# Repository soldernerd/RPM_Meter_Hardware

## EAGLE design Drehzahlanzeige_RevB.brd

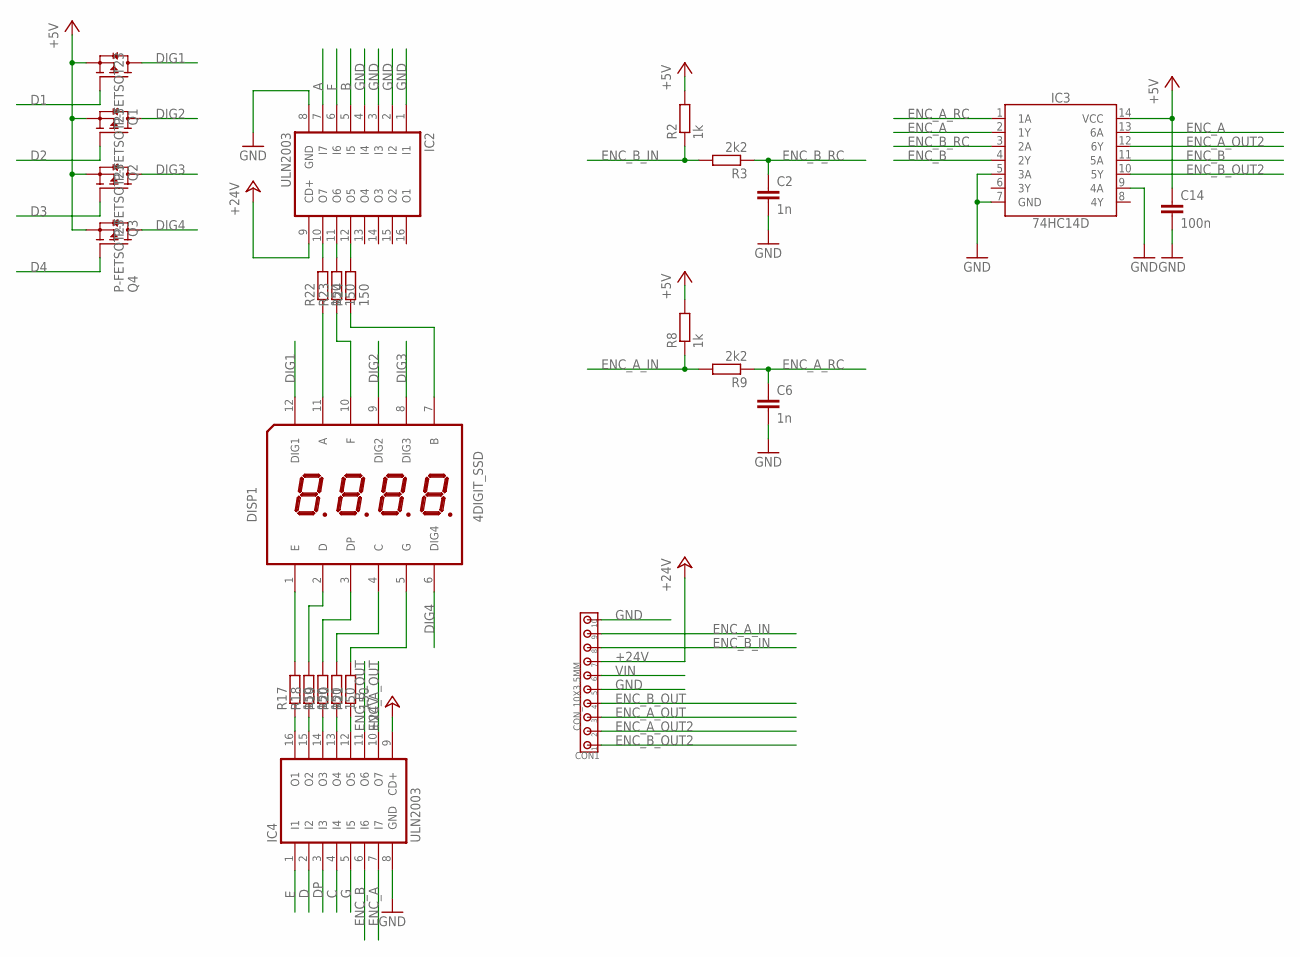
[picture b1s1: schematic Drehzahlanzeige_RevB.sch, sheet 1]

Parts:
C2, C6: 1n; C0805
C14: 100n; C0805
CON1: CON_10X3.5MM; 3.5MM_10X
DISP1: 4DIGIT_SSD
IC2, IC4: ULN2003; SO16
IC3: 74HC14D; SO14
Q1, Q2, Q3, Q4: P-FETSOT23; SOT23
R2, R8: 1k; R0805
R3, R9: 2k2; R0805
R17, R18, R19, R20, R21, R22, R23, R24: 150; R0805

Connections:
+5V: C14.1, IC3.14 (VCC), Q1.2 (S), Q2.2 (S), Q3.2 (S), Q4.2 (S), R2.2, R8.2; also elsewhere on the board
+24V: CON1.7, IC2.9 (CD+), IC4.9 (CD+); also elsewhere on the board
A: IC2.7 (I7); also elsewhere on the board
B: IC2.5 (I5); also elsewhere on the board
C: IC4.4 (I4); also elsewhere on the board
D: IC4.2 (I2); also elsewhere on the board
D1: Q1.1 (G); also elsewhere on the board
D2: Q2.1 (G); also elsewhere on the board
D3: Q3.1 (G); also elsewhere on the board
D4: Q4.1 (G); also elsewhere on the board
DIG1: DISP1.12 (DIG1), Q1.3 (D)
DIG2: DISP1.9 (DIG2), Q2.3 (D)
DIG3: DISP1.8 (DIG3), Q3.3 (D)
DIG4: DISP1.6 (DIG4), Q4.3 (D)
DP: IC4.3 (I3); also elsewhere on the board
E: IC4.1 (I1); also elsewhere on the board
ENC_A: IC3.2 (1Y), IC3.13 (6A), IC4.7 (I7); also elsewhere on the board
ENC_A_IN: CON1.9, R8.1, R9.2
ENC_A_OUT: CON1.3, IC4.10 (O7)
ENC_A_OUT2: CON1.2, IC3.12 (6Y)
ENC_A_RC: C6.1, IC3.1 (1A), R9.1
ENC_B: IC3.4 (2Y), IC3.11 (5A), IC4.6 (I6); also elsewhere on the board
ENC_B_IN: CON1.8, R2.1, R3.2
ENC_B_OUT: CON1.4, IC4.11 (O6)
ENC_B_OUT2: CON1.1, IC3.10 (5Y)
ENC_B_RC: C2.1, IC3.3 (2A), R3.1
F: IC2.6 (I6); also elsewhere on the board
G: IC4.5 (I5); also elsewhere on the board
GND: C2.2, C6.2, C14.2, CON1.5, CON1.10, IC2.1 (I1), IC2.2 (I2), IC2.3 (I3), IC2.4 (I4), IC2.8 (GND), IC3.5 (3A), IC3.7 (GND), IC3.9 (4A), IC4.8 (GND); also elsewhere on the board
unnamed: DISP1.1 (E), R17.2
unnamed: DISP1.2 (D), R18.2
unnamed: DISP1.3 (DP), R19.2
unnamed: DISP1.4 (C), R20.2
unnamed: DISP1.5 (G), R21.2
unnamed: DISP1.11 (A), R22.1
unnamed: DISP1.10 (F), R23.1
unnamed: DISP1.7 (B), R24.1
unnamed: IC4.16 (O1), R17.1
unnamed: IC4.15 (O2), R18.1
unnamed: IC4.14 (O3), R19.1
unnamed: IC4.13 (O4), R20.1
unnamed: IC4.12 (O5), R21.1
unnamed: IC2.10 (O7), R22.2
unnamed: IC2.11 (O6), R23.2
unnamed: IC2.12 (O5), R24.2
VIN: CON1.6; also elsewhere on the board

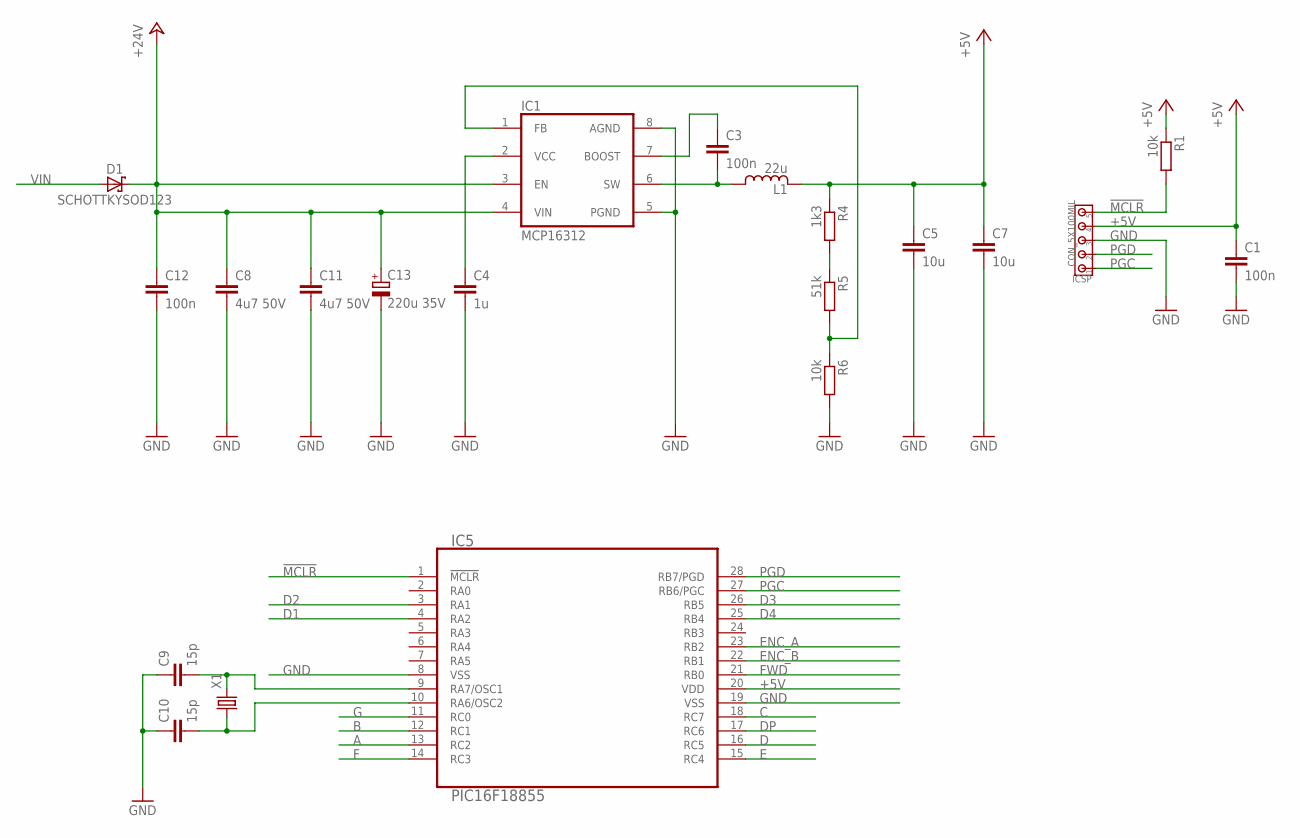
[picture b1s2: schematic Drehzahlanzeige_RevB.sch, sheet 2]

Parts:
C1, C3, C12: 100n; C0805
C4: 1u; C0805
C5, C7: 10u; C0805
C8, C11: 4u7 50V; C1206
C9, C10: 15p; C0805
C13: 220u 35V; 8MM
D1: SCHOTTKYSOD123; SOD123
IC1: MCP16312; MSOP8
IC5: PIC16F18855; SO28W
ICSP: CON_5X100MIL; 100MIL_5X
L1: 22u; LPS4018
R1, R6: 10k; R0805
R4: 1k3; R0805
R5: 51k; R0805
X1: CRYSTAL5X3.2MM; 5X3.2MM

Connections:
!MCLR!: IC5.1 (!MCLR!), ICSP.5, R1.2
+5V: C1.1, C5.1, C7.1, IC5.20 (VDD), ICSP.4, L1.2, R1.1, R4.1; also elsewhere on the board
+24V: C8.1, C11.1, C12.1, C13.+, D1.C, IC1.3 (EN), IC1.4 (VIN); also elsewhere on the board
A: IC5.13 (RC2); also elsewhere on the board
B: IC5.12 (RC1); also elsewhere on the board
BOOST: C3.1, IC1.7 (BOOST)
C: IC5.18 (RC7); also elsewhere on the board
D: IC5.16 (RC5); also elsewhere on the board
D1: IC5.4 (RA2); also elsewhere on the board
D2: IC5.3 (RA1); also elsewhere on the board
D3: IC5.26 (RB5); also elsewhere on the board
D4: IC5.25 (RB4); also elsewhere on the board
DP: IC5.17 (RC6); also elsewhere on the board
E: IC5.15 (RC4); also elsewhere on the board
ENC_A: IC5.23 (RB2); also elsewhere on the board
ENC_B: IC5.22 (RB1); also elsewhere on the board
F: IC5.14 (RC3); also elsewhere on the board
FWD: IC5.21 (RB0)
G: IC5.11 (RC0); also elsewhere on the board
GND: C1.2, C4.2, C5.2, C7.2, C8.2, C9.1, C10.1, C11.2, C12.2, C13.-, IC1.5 (PGND), IC1.8 (AGND), IC5.8 (VSS), IC5.19 (VSS), ICSP.3, R6.2; also elsewhere on the board
unnamed: IC1.1 (FB), R5.2, R6.1
unnamed: R4.2, R5.1
unnamed: C4.1, IC1.2 (VCC)
unnamed: C10.2, IC5.10 (RA6/OSC2), X1.1
unnamed: C9.2, IC5.9 (RA7/OSC1), X1.2
PGC: IC5.27 (RB6/PGC), ICSP.1
PGD: IC5.28 (RB7/PGD), ICSP.2
RA4: IC5.6 (RA4)
SWITCH: C3.2, IC1.6 (SW), L1.1
VIN: D1.A; also elsewhere on the board

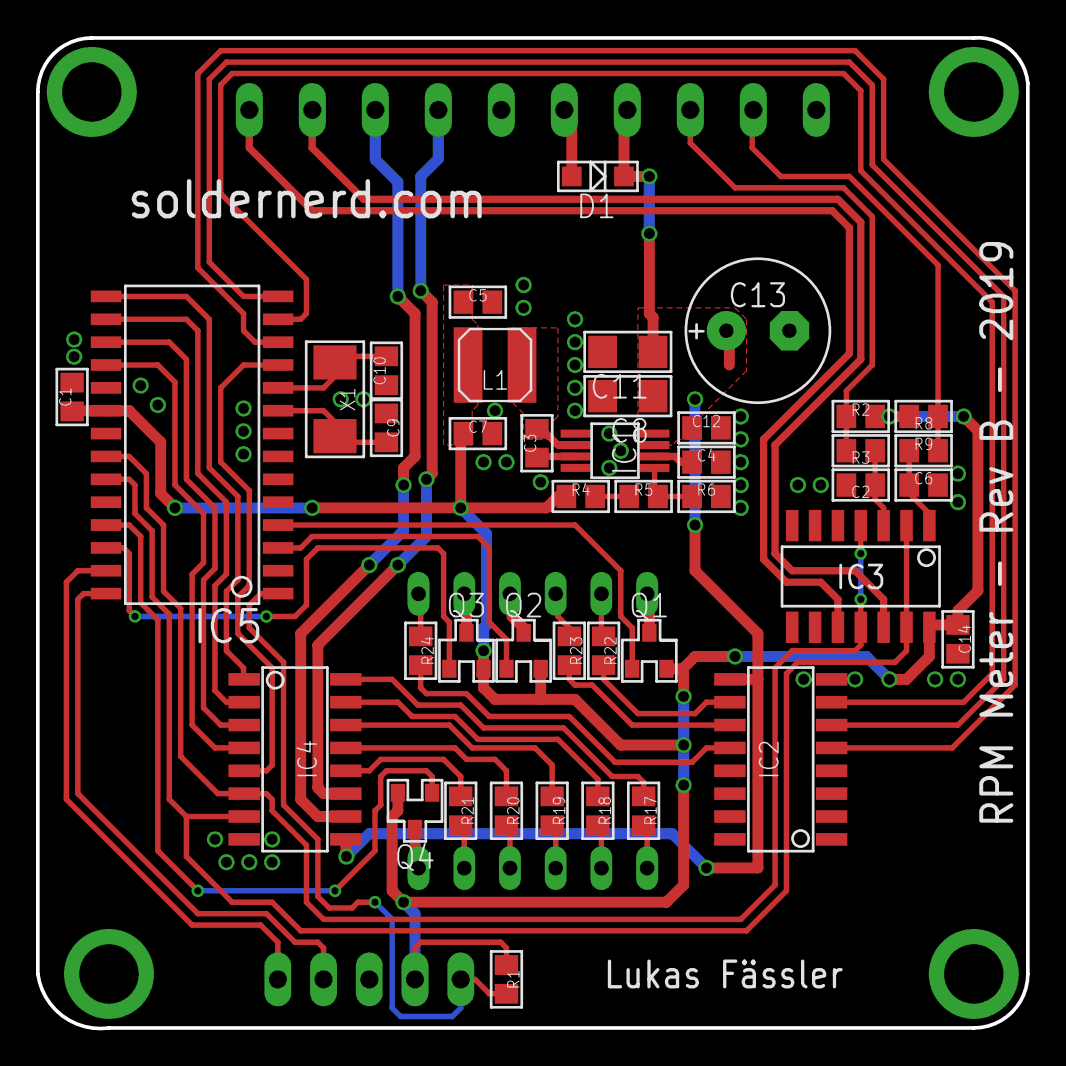
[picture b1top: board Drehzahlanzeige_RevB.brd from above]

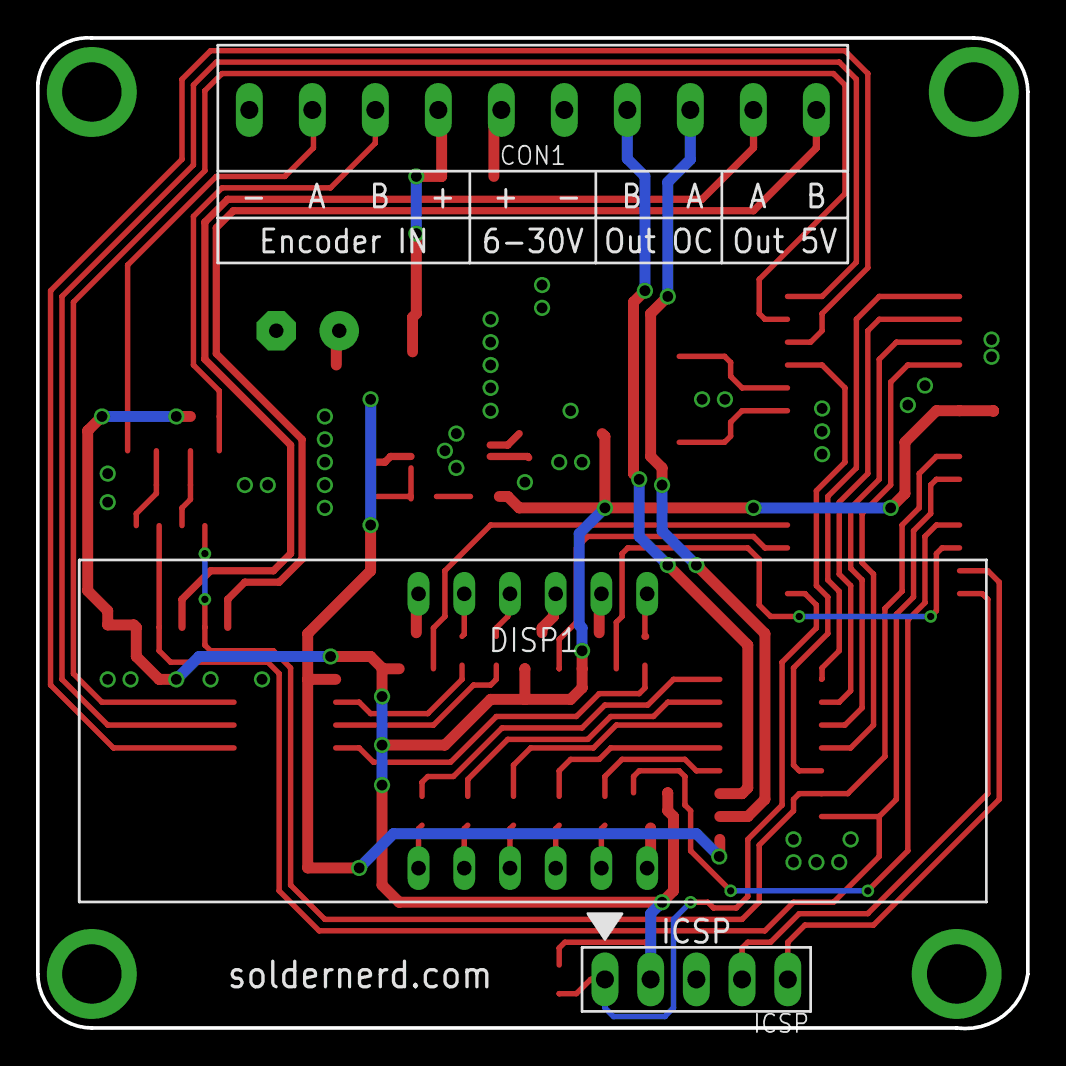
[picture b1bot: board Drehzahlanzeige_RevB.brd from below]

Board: 2 copper layers, 55.0 x 55.0 mm, 45 parts (3 on the bottom side), 56 nets.

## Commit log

2019-01-06 Revision A final
2019-01-06 zip file with all gerbers for dirtypcbs.com added
2020-12-08 Revision B with different physical layout and extra output
